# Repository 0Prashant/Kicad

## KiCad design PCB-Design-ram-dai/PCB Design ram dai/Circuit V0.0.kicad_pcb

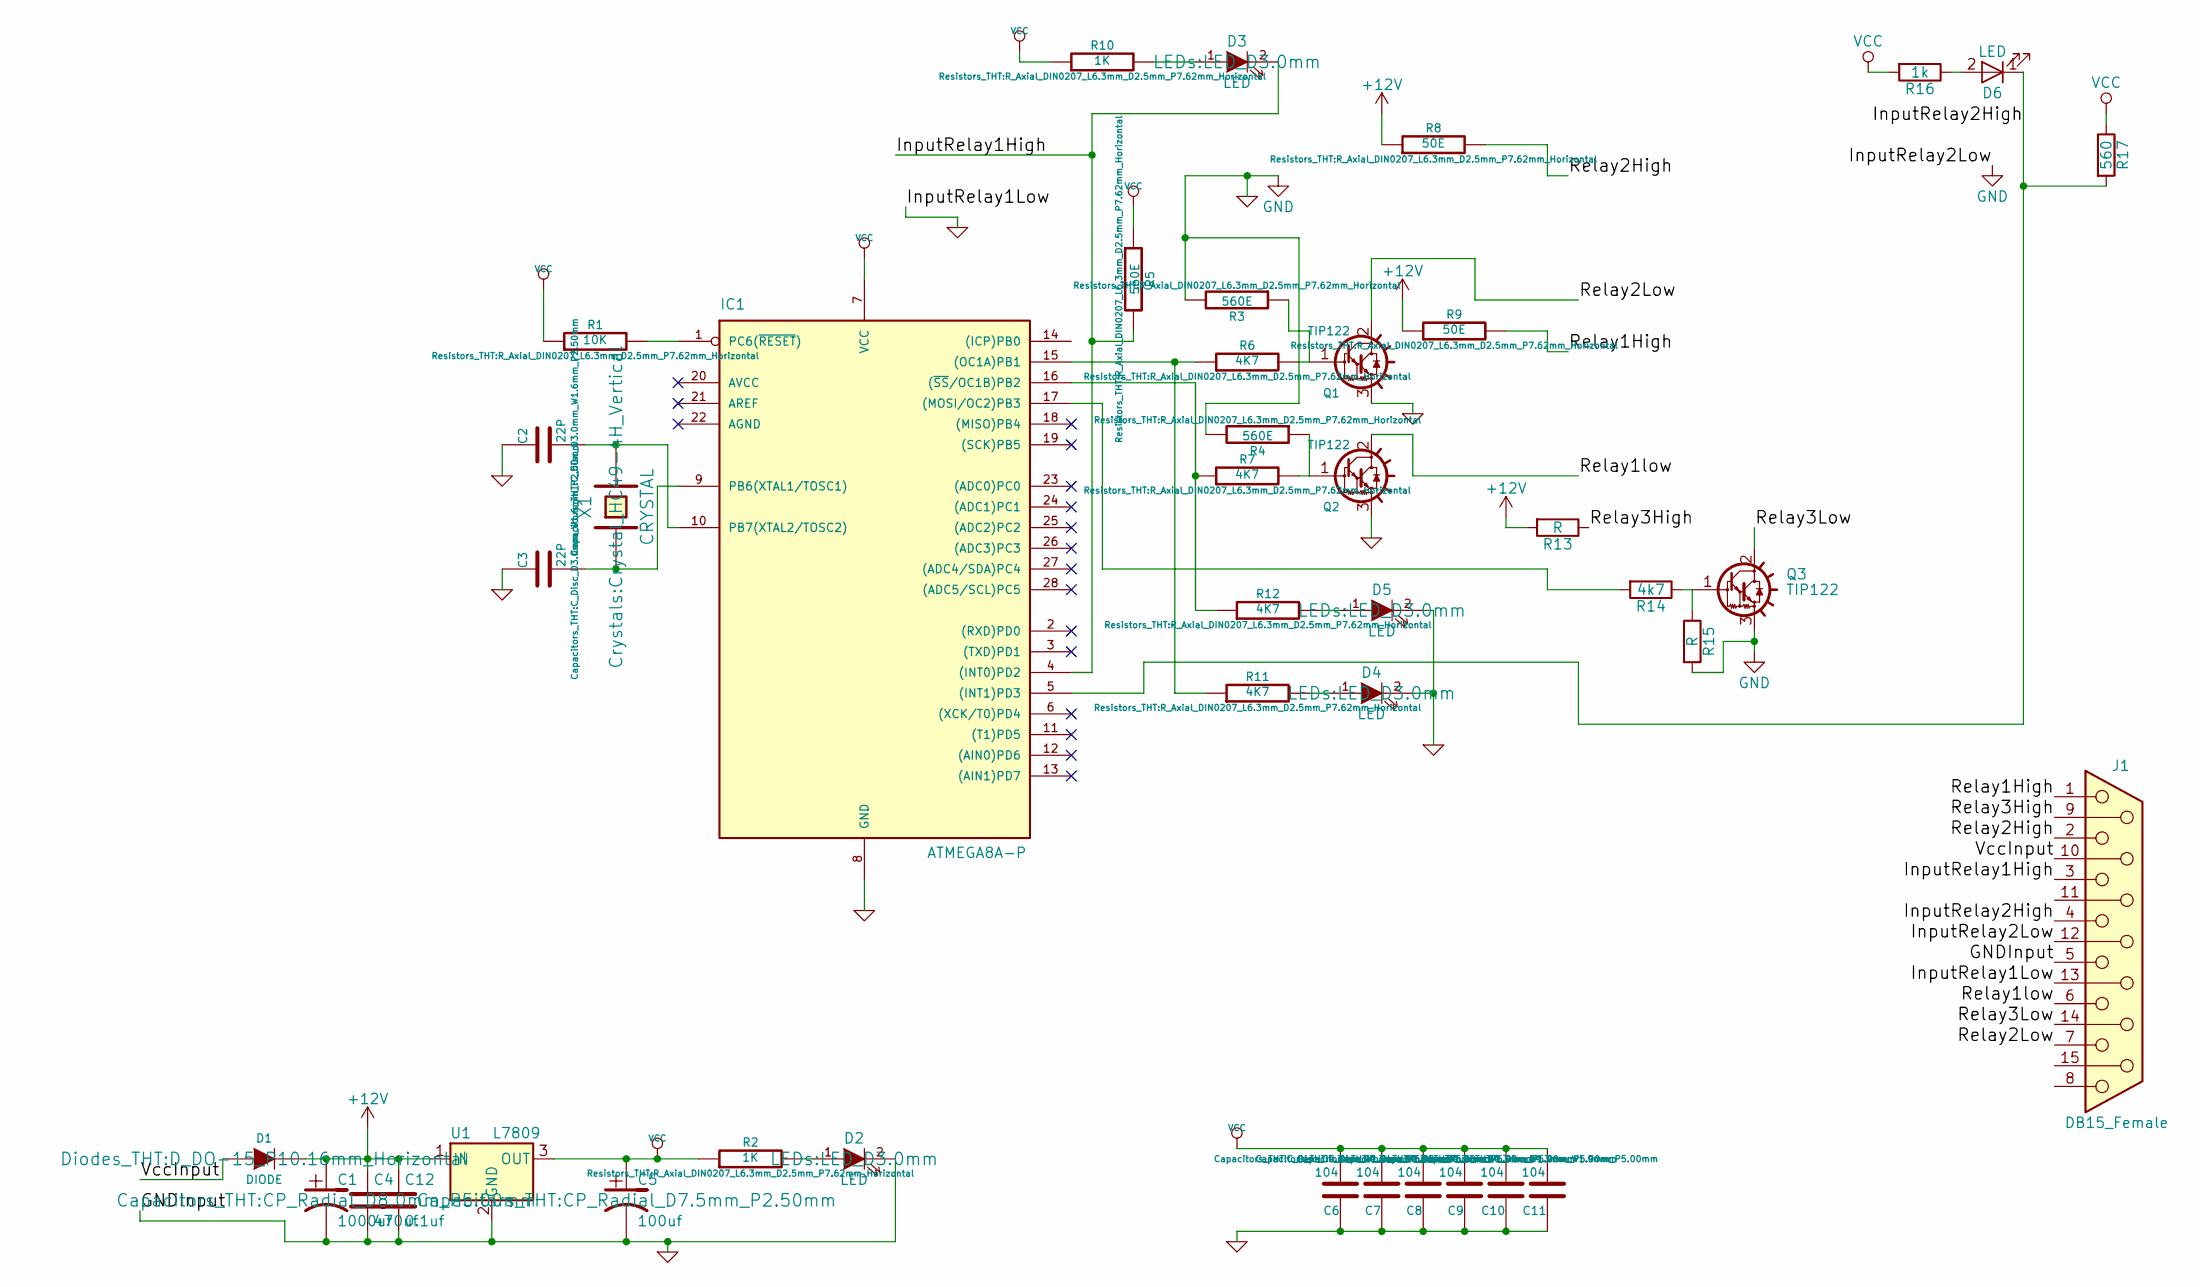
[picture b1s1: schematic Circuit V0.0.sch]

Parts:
C1: 1000uf; CP_Radial_D8.0mm_P5.00mm
C2, C3: 22P; C_Disc_D3.0mm_W1.6mm_P2.50mm
C4: 470uf; CP_Radial_D8.0mm_P3.80mm
C5: 100uf; CP_Radial_D7.5mm_P2.50mm
C6, C7, C8, C9, C10, C11: 104; C_Disc_D4.3mm_W1.9mm_P5.00mm
C12: 0.1uf; C_Disc_D4.3mm_W1.9mm_P5.00mm
D1: DIODE; D_DO-15_P10.16mm_Horizontal
D2, D3, D4, D5, D6: LED; LED_D3.0mm
IC1: ATMEGA8A-P; DIL28
J1: DB15_Female; DB15FC
Q1, Q2: TIP122; TO220
Q3: TIP122; TO-220_Vertical
R1: 10K; R_Axial_DIN0207_L6.3mm_D2.5mm_P7.62mm_Horizontal
R2, R10: 1K; R_Axial_DIN0207_L6.3mm_D2.5mm_P7.62mm_Horizontal
R3, R4, R5: 560E; R_Axial_DIN0207_L6.3mm_D2.5mm_P7.62mm_Horizontal
R6, R7, R11, R12: 4K7; R_Axial_DIN0207_L6.3mm_D2.5mm_P7.62mm_Horizontal
R8, R9: 50E; R_Axial_DIN0207_L6.3mm_D2.5mm_P7.62mm_Horizontal
R13, R15: R; R_Axial_DIN0207_L6.3mm_D2.5mm_P7.62mm_Horizontal
R14: 4k7; R_Axial_DIN0207_L6.3mm_D2.5mm_P7.62mm_Horizontal
R16: 1k; R_Axial_DIN0207_L6.3mm_D2.5mm_P7.62mm_Horizontal
R17: 560; R_Axial_DIN0207_L6.3mm_D2.5mm_P7.62mm_Horizontal
U1: L7809; TO-220
X1: CRYSTAL; Crystal_HC49-4H_Vertical

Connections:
+12V: C1.1, C4.1, C12.1, D1.2 (K), R8.1, R9.1, R13.2, U1.1 (IN)
/InputRelay1High: D3.2 (K), IC1.4 ((INT0)PD2), J1.3, R5.2
/InputRelay2High: D6.1 (K), IC1.5 ((INT1)PD3), J1.4, R17.2
/Relay1High: J1.1, R9.2
/Relay1low: J1.6, Q2.2 (C)
/Relay2High: J1.2, R8.2
/Relay2Low: J1.7, Q1.2 (C)
/Relay3High: J1.9, R13.1
/Relay3Low: J1.14, Q3.2 (C)
/VccInput: D1.1 (A), J1.10
GND: C1.2, C2.1, C3.1, C4.2, C5.2, C6.1, C7.1, C8.1, C9.1, C10.1, C11.1, C12.2, D2.2 (K), D4.2 (K), D5.2 (K), IC1.8 (GND), J1.5, J1.12, J1.13, Q1.3 (E), Q2.3 (E), Q3.3 (E), R3.2, R4.2, R15.2, U1.2 (GND)
unnamed: C2.2, IC1.10 (PB7(XTAL2/TOSC2)), X1.2
unnamed: C3.2, IC1.9 (PB6(XTAL1/TOSC1)), X1.1
unnamed: D2.1 (A), R2.2
unnamed: D3.1 (A), R10.2
unnamed: D4.1 (A), R11.2
unnamed: D5.1 (A), R12.2
unnamed: D6.2 (A), R16.1
unnamed: IC1.1 (PC6(~RESET~)), R1.2
unnamed: IC1.15 ((OC1A)PB1), R6.1, R11.1
unnamed: IC1.16 ((~SS~/OC1B)PB2), R7.1, R12.1
unnamed: IC1.17 ((MOSI/OC2)PB3), R14.2
unnamed: Q1.1 (B), R3.1, R6.2
unnamed: Q2.1 (B), R4.1, R7.2
unnamed: Q3.1 (B), R14.1, R15.1
VCC: C5.1, C6.2, C7.2, C8.2, C9.2, C10.2, C11.2, IC1.7 (VCC), R1.1, R2.1, R5.1, R10.1, R16.2, R17.1, U1.3 (OUT)

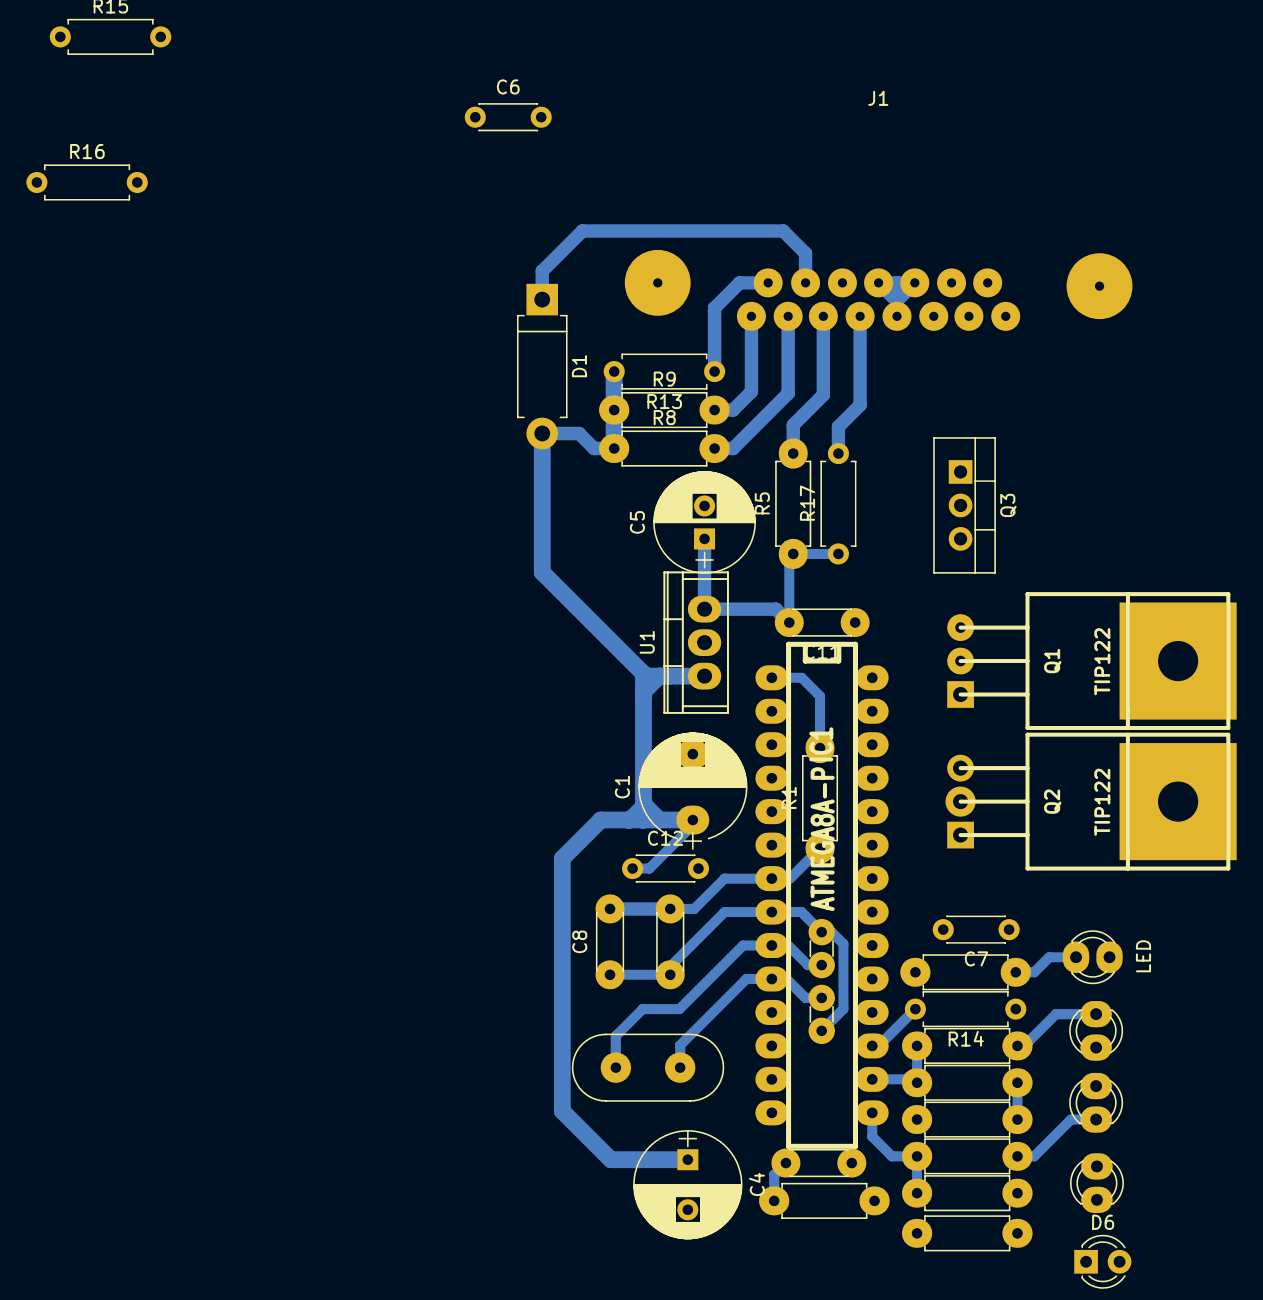
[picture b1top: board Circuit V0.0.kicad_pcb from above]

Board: 2 copper layers, 42 parts (0 on the bottom side), 26 nets.

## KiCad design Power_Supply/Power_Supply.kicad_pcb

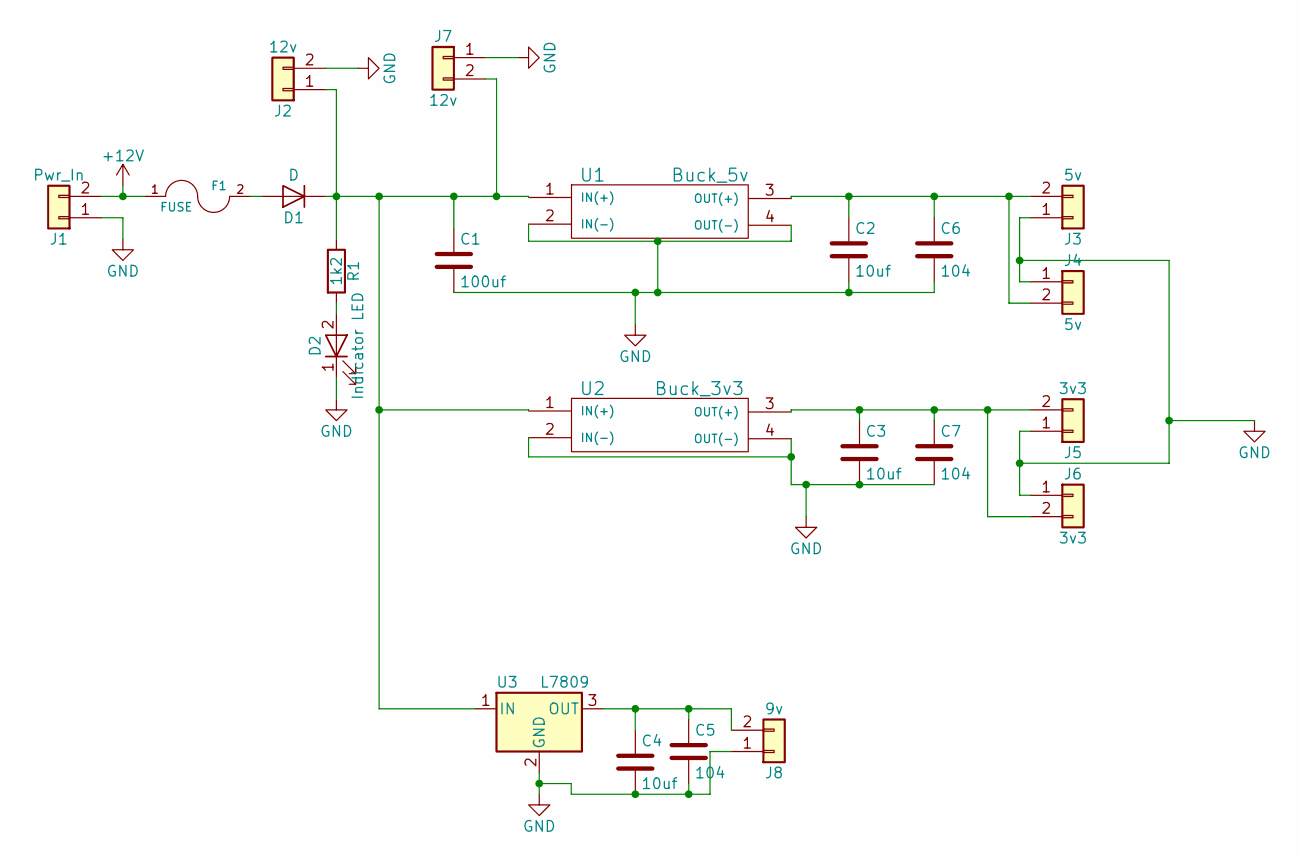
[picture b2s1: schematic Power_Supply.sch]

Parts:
C1: 100uf; Capacitor_100uF
C2, C3, C4: 10uf; Capacitor_10uF
C5, C6, C7: 104; Capacitor_Disc_Small
D1: D; Diode_Medium
D2: Indicator LED; LED_D3.0mm
F1: FUSE; Fuse_Holder
J1: Pwr_In; Solar_Connector
J2: 12v; Solar_Connector
J3, J4: 5v; Connector_Bornier_2
J5, J6: 3v3; Connector_Bornier_2
J7: 12v; Connector_Bornier_2
J8: 9v; Connector_Bornier_2
R1: 1k2; Resistor_small
U1: Buck_5v; Buck_Regulator
U2: Buck_3v3; Buck_Regulator
U3: L7809; Voltage_Regulators

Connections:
+12V: F1.1, J1.2
GND: C1.2, C2.2, C3.2, C4.2, C5.2, C6.2, C7.2, D2.1 (K), J1.1, J2.2, J3.1, J4.1, J5.1, J6.1, J7.1, J8.1, U1.2 (IN(-)), U1.4 (OUT(-)), U2.2 (IN(-)), U2.4 (OUT(-)), U3.2 (GND)
unnamed: C1.1, D1.1 (K), J2.1, J7.2, R1.1, U1.1 (IN(+)), U2.1 (IN(+)), U3.1 (IN)
unnamed: C2.1, C6.1, J3.2, J4.2, U1.3 (OUT(+))
unnamed: C3.1, C7.1, J5.2, J6.2, U2.3 (OUT(+))
unnamed: C4.1, C5.1, J8.2, U3.3 (OUT)
unnamed: D1.2 (A), F1.2
unnamed: D2.2 (A), R1.2

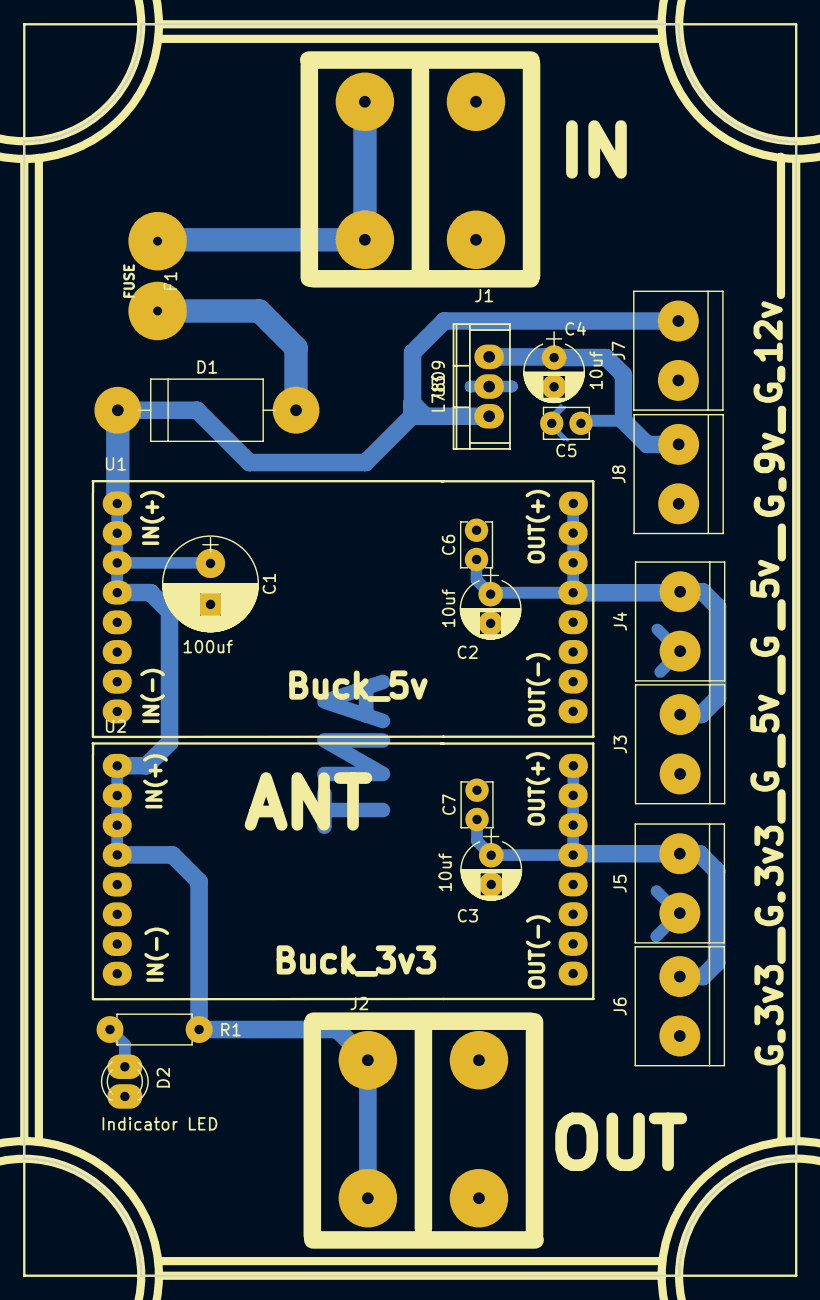
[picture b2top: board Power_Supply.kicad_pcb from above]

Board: 2 copper layers, 66.0 x 107.0 mm, 22 parts (0 on the bottom side), 8 nets.

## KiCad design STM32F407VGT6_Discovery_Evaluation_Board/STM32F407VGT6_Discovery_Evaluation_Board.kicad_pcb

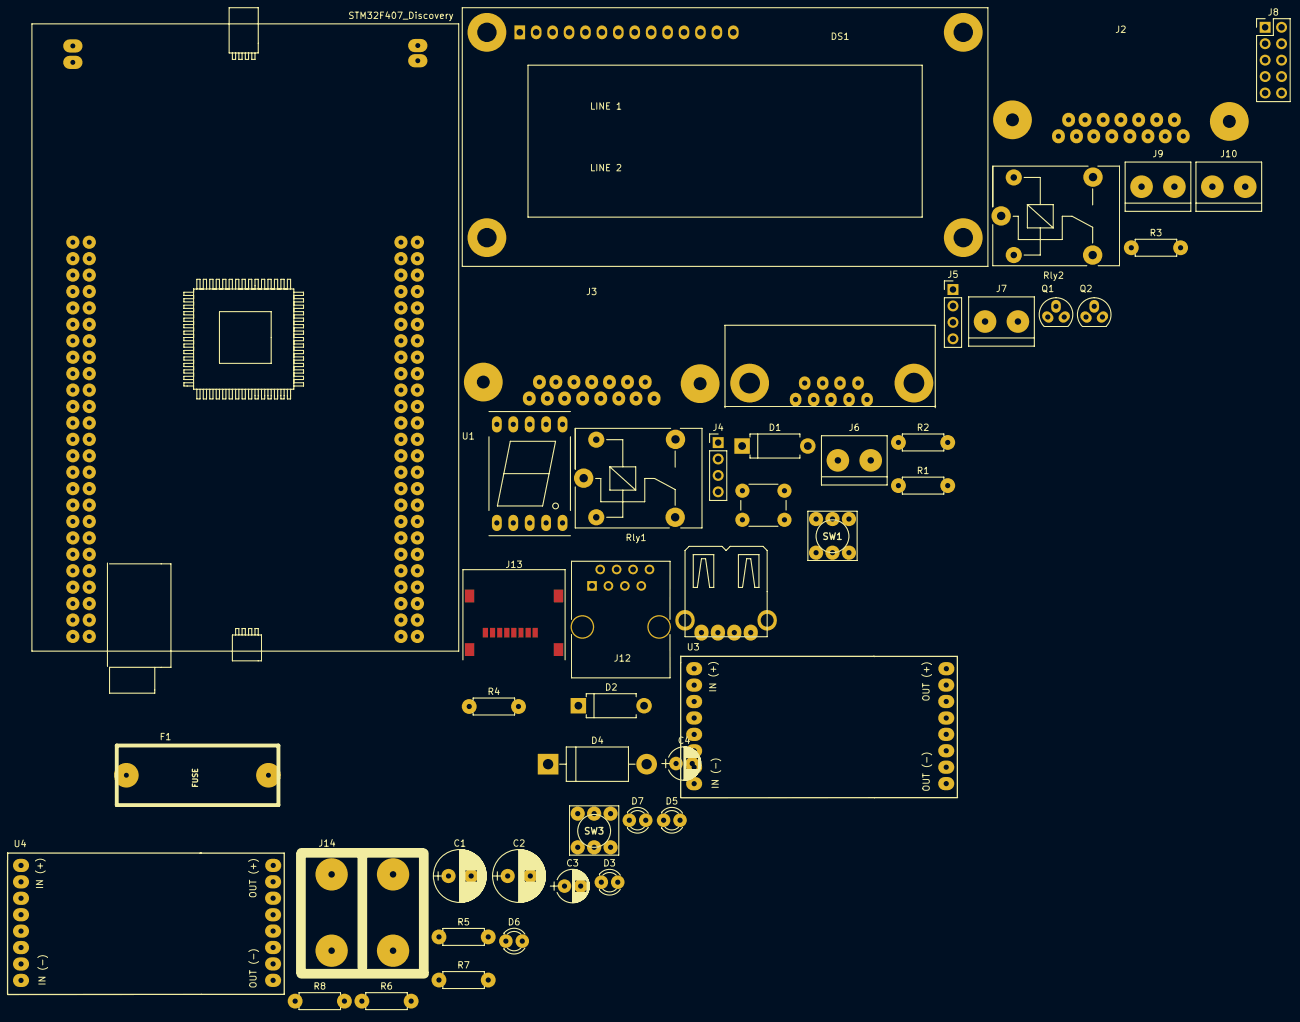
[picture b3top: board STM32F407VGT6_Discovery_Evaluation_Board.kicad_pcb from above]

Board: 2 copper layers, 46 parts (0 on the bottom side), 23 nets, no tracks yet.

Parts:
C1, C2: C; Capacitor_100uF
C3, C4: C; Capacitor_10uF
D1, D2: D; Diode_Small
D3, D5, D6, D7: LED; LED_D3.0mm
D4: D; Diode_Medium
DS1: LCD16X2; LCD_ALPHA
F1: FUSE; Fuse_Holder
J1: encode; Connector_DB_9
J2: motor; Connector_DB15
J3: other; Connector_DB15
J4: uart; Pin_Header_Straight_1x04_Pitch2.54mm
J5: i2c; Pin_Header_Straight_1x04_Pitch2.54mm
J6, J7: relay; Connector_Bornier_2
J8: vcc gnd; Pin_Header_Straight_2x05_Pitch2.54mm
J9: 3v3; Connector_Bornier_2
J10: 5v; Connector_Bornier_2
J11: USB_A; Connector_USB
J12: RJ45; RJ45_8
J13: Micro_SD_Card; MicroSd_Wurth_693072010801
J14: Power_In; Solar_Connector
Q1, Q2: BC547
R1, R2, R3, R4, R5, R6, R7, R8: R; Resistor_small
Rly1, Rly2: 6V_Relay; Relay_6V
SW1: dip; DIP_Switch
SW2: Push; Push_Button
SW3: SW_DIP_x01; DIP_Switch
U1: 7SEGMENT_CC; 7SegmentLED_LTS6760_LTS6780
U2: STM32F407_Discovery
U3, U4: Buck; Buck_Regulator

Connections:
+3V3: C3.1, R8.1, U4.3
+5V: C4.1, R7.1, U3.3
+12V: C1.1, C2.1, D4.1, R6.1, U3.1, U4.1
GND: C1.2, C2.2, C3.2, C4.2, D3.1, D5.1, D6.1, D7.1, J14.1, Q1.3, Q2.3, R1.2, R2.2, U3.2, U3.4, U4.2, U4.4
unnamed: D1.1, Rly1.5
unnamed: D1.2, Q1.1, Rly1.1
unnamed: D2.1, Rly2.5
unnamed: D2.2, Q2.1, Rly2.1
unnamed: D3.2, R5.2
unnamed: D4.2, F1.2
unnamed: D5.2, R6.2
unnamed: D6.2, R7.2
unnamed: D7.2, R8.2
unnamed: F1.1, SW3.2
unnamed: J6.1, Rly1.3
unnamed: J6.2, Rly1.2
unnamed: J7.1, Rly2.3
unnamed: J7.2, Rly2.2
unnamed: J14.2, R5.1, SW3.1
unnamed: Q1.2, R3.1
unnamed: Q2.2, R4.1
unnamed: R1.1, R3.2
unnamed: R2.1, R4.2

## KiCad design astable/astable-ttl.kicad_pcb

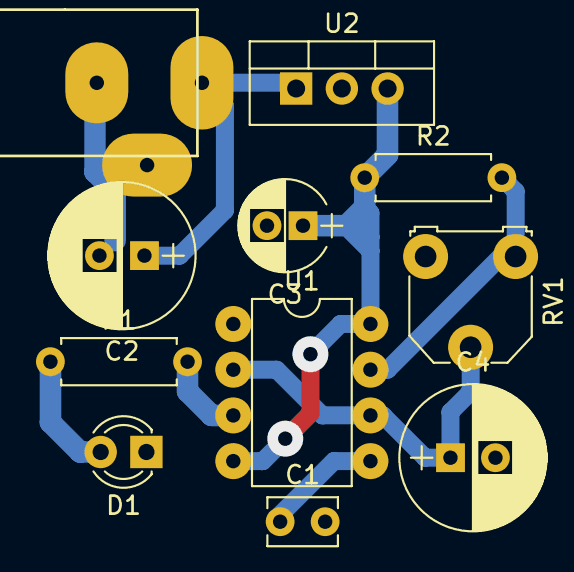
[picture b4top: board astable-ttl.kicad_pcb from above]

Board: 2 copper layers, 11 parts (0 on the bottom side), 8 nets.

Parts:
C1: 0.1UF; C_Disc_D3.8mm_W2.6mm_P2.50mm
C2, C4: 100UF; CP_Radial_D8.0mm_P2.50mm
C3: 10UF; CP_Radial_D5.0mm_P2.00mm
D1: LED; LED_D3.0mm
R1: 330; R_Axial_DIN0207_L6.3mm_D2.5mm_P7.62mm_Horizontal
R2: 5K; R_Axial_DIN0207_L6.3mm_D2.5mm_P7.62mm_Horizontal
RV1: POT; Potentiometer_Triwood_RM-065
U1: NE555; DIP-8_W7.62mm
U2: L7805; TO-220_Vertical
U3: Barrel_jack

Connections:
/VCC: C3.1, R2.1, U1.4, U1.8, U2.3
GND: C1.2, C2.2, C3.2, C4.2, D1.1, U1.1, U2.2, U3.2
unnamed: C1.1, U1.5
unnamed: C2.1, U2.1, U3.1
unnamed: C4.1, RV1.2, U1.2, U1.6
unnamed: D1.2, R1.1
unnamed: R1.2, U1.3
unnamed: R2.2, RV1.1, U1.7

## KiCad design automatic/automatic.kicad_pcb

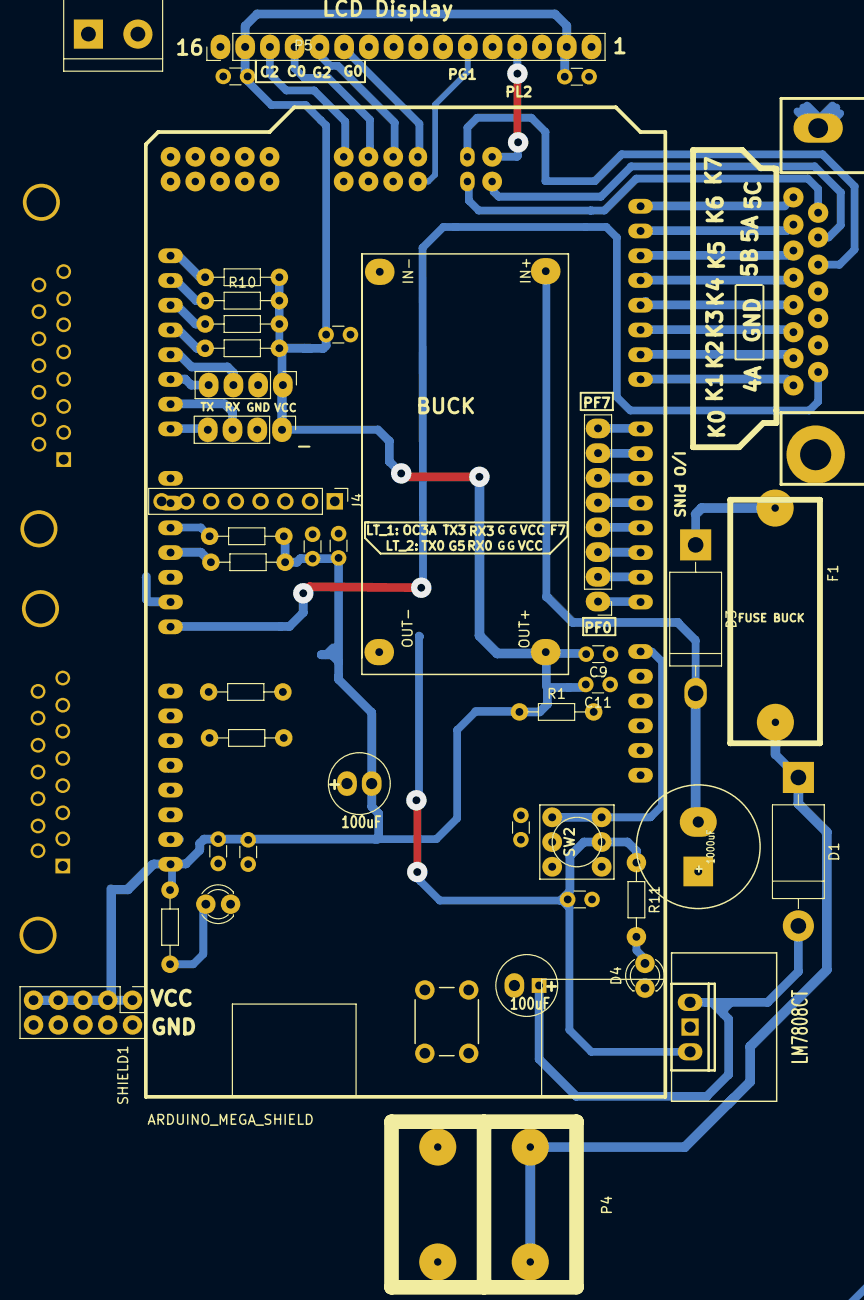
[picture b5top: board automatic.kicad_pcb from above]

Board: 2 copper layers, 46 parts (0 on the bottom side), 64 nets.

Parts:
C1, C14: 100uF; c_100
C2: 104Pf; C_Disc_D3.0mm_W1.6mm_P2.50mm
C3: 10uF; C_Disc_D3.0mm_W1.6mm_P2.50mm
C4, C5, C6, C7, C8, C9, C10, C11, C12: 104; C_Disc_D3.0mm_W1.6mm_P2.50mm
C13: 1000uF; c_1000
D1, D3: DIODE; D_DO-201AD_P15.24mm_Horizontal
D2, D4: LED; LED_D3.0mm
F1: FUSE BUCK; FUSE
J1: DB15; DB15MC
J2: LINE TRACKER; DB15FC
J3: LCD Display; Pin_Header_Straight_1x16_Pitch2.54mm
J4: CONN_01X08; Pin_Header_Straight_1x08_Pitch2.54mm
J5: DB15; DB15FC
J7: I/O_2; Pin_Header_Straight_1x08_Pitch2.54mm
P1: BlueTh2; Pin_Header_Straight_1x04_Pitch2.54mm
P2: BlueTh3; Pin_Header_Straight_1x04_Pitch2.54mm
P3: CONN_5X2; Pin_Header_Straight_2x05_Pitch2.54mm
P4: BATTERY; SOLAR_CONNECTOR
P5: BUCK REG; Buck_reg_mod
P6: CONN_2; bornier2
R1, R3, R4, R5, R6, R8, R10: 10K; R_Axial_DIN0204_L3.6mm_D1.6mm_P7.62mm_Horizontal
R2, R11: 330; R_Axial_DIN0204_L3.6mm_D1.6mm_P7.62mm_Horizontal
R7, R9: 1K; R_Axial_DIN0204_L3.6mm_D1.6mm_P7.62mm_Horizontal
SHIELD1: ARDUINO_MEGA_SHIELD; ARUDINO_MEGA_SHIELD
SW1: SW_PUSH; SW_PUSH_6mm
SW2: SW_PUSH; SPST_SMALL
U1: LM7808CT; LM78_heatsink

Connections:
/9V: C3.1, R11.1, SW2.1, U1.3
/12V: D1.1, F1.1, P4.1
/E: J3.11, SHIELD1.40
/GND: C1.2, C2.2, C3.2, C4.2, C5.1, C6.2, C7.1, C8.2, C9.1, C10.2, C11.1, C12.2, C13.1, C14.1, D2.1, D4.1, J1.10, J1.11, J1.12, J3.1, J3.12, J3.16, J5.15, P1.2, P2.2, P3.2, P3.4, P3.6, P3.8, P3.10, P4.2, P5.1, P5.3, SHIELD1.GND1, SHIELD1.GND2, SHIELD1.GND3, SW1.2, U1.2
/INT0: R8.1, SHIELD1.21
/INT1: R10.1, SHIELD1.20
/INT2: J5.13, R3.1, SHIELD1.19
/INT3: J5.6, R4.1, SHIELD1.18
/INT4: J5.14, R5.1, SHIELD1.2
/INT5: J5.7, R6.1, SHIELD1.3
/JPULSE1: J2.12, SHIELD1.9
/JPULSE2: J2.4, SHIELD1.10
/OC4A: J1.9, SHIELD1.6
/OC4C: R9.1, SHIELD1.8
/OC5A: J1.14, SHIELD1.46
/OC5B: J1.13, SHIELD1.45
/OC5C: J1.15, SHIELD1.44
/PA0: J5.2, SHIELD1.22
/PA1: J5.1, SHIELD1.23
/PA2: J5.10, SHIELD1.24
/PA3: J5.9, SHIELD1.25
/PA4: J5.3, SHIELD1.26
/PA5: J5.11, SHIELD1.27
/PA6: J2.14, P6.1, SHIELD1.28
/PA7: J2.6, P6.2, SHIELD1.29
/PC0: J3.4, J4.8, SHIELD1.37
/PC1: J4.7, SHIELD1.36
/PC2: J3.3, J4.6, SHIELD1.35
/PC3: J4.5, SHIELD1.34
/PF0: J7.1, SHIELD1.AD0
/PF1: J7.2, SHIELD1.AD1
/PF2: J7.3, SHIELD1.AD2
/PF3: J7.4, SHIELD1.AD3
/PF4: J7.5, SHIELD1.AD4
/PF5: J7.6, SHIELD1.AD5
/PF6: J7.7, SHIELD1.AD6
/PF7: J7.8, SHIELD1.AD7
/PG0: J3.6, SHIELD1.41
/PG2: J3.5, SHIELD1.39
/PK0: J1.1, SHIELD1.AD8
/PK1: J1.2, SHIELD1.AD9
/PK2: J1.3, SHIELD1.AD10
/PK3: J1.4, SHIELD1.AD11
/PK4: J1.5, SHIELD1.AD12
/PK5: J1.6, SHIELD1.AD13
/PK6: J1.7, SHIELD1.AD14
/PK7: J1.8, SHIELD1.AD15
/PL2: J3.13, SHIELD1.47
/RESET: C2.1, R1.2, SHIELD1.RST, SW1.1
/RX0: J2.3, SHIELD1.0
/RX2: J2.2, P1.3, SHIELD1.17
/RX3: P2.3, SHIELD1.15
/TX0: J2.11, SHIELD1.1
/TX2: J2.10, P1.4, SHIELD1.16
/TX3: P2.4, SHIELD1.14
/UEN1: J2.13, SHIELD1.11
/UEN2: J2.5, SHIELD1.12
/VCC: C4.1, C5.2, C6.1, C7.2, C8.1, C9.2, C10.1, C11.2, C12.1, C14.2, J3.2, J3.15, J5.8, P1.1, P2.1, P3.1, P3.3, P3.5, P3.7, P3.9, P5.4, R1.1, R2.1, R3.2, R4.2, R5.2, R6.2, R8.2, R10.2, SHIELD1.AREF
/VIN: SHIELD1.V_IN, SW2.2
unnamed: C1.1, D1.2, U1.1
unnamed: C13.2, D3.2, P5.2
unnamed: D2.2, R2.2
unnamed: D3.1, F1.2
unnamed: D4.2, R11.2

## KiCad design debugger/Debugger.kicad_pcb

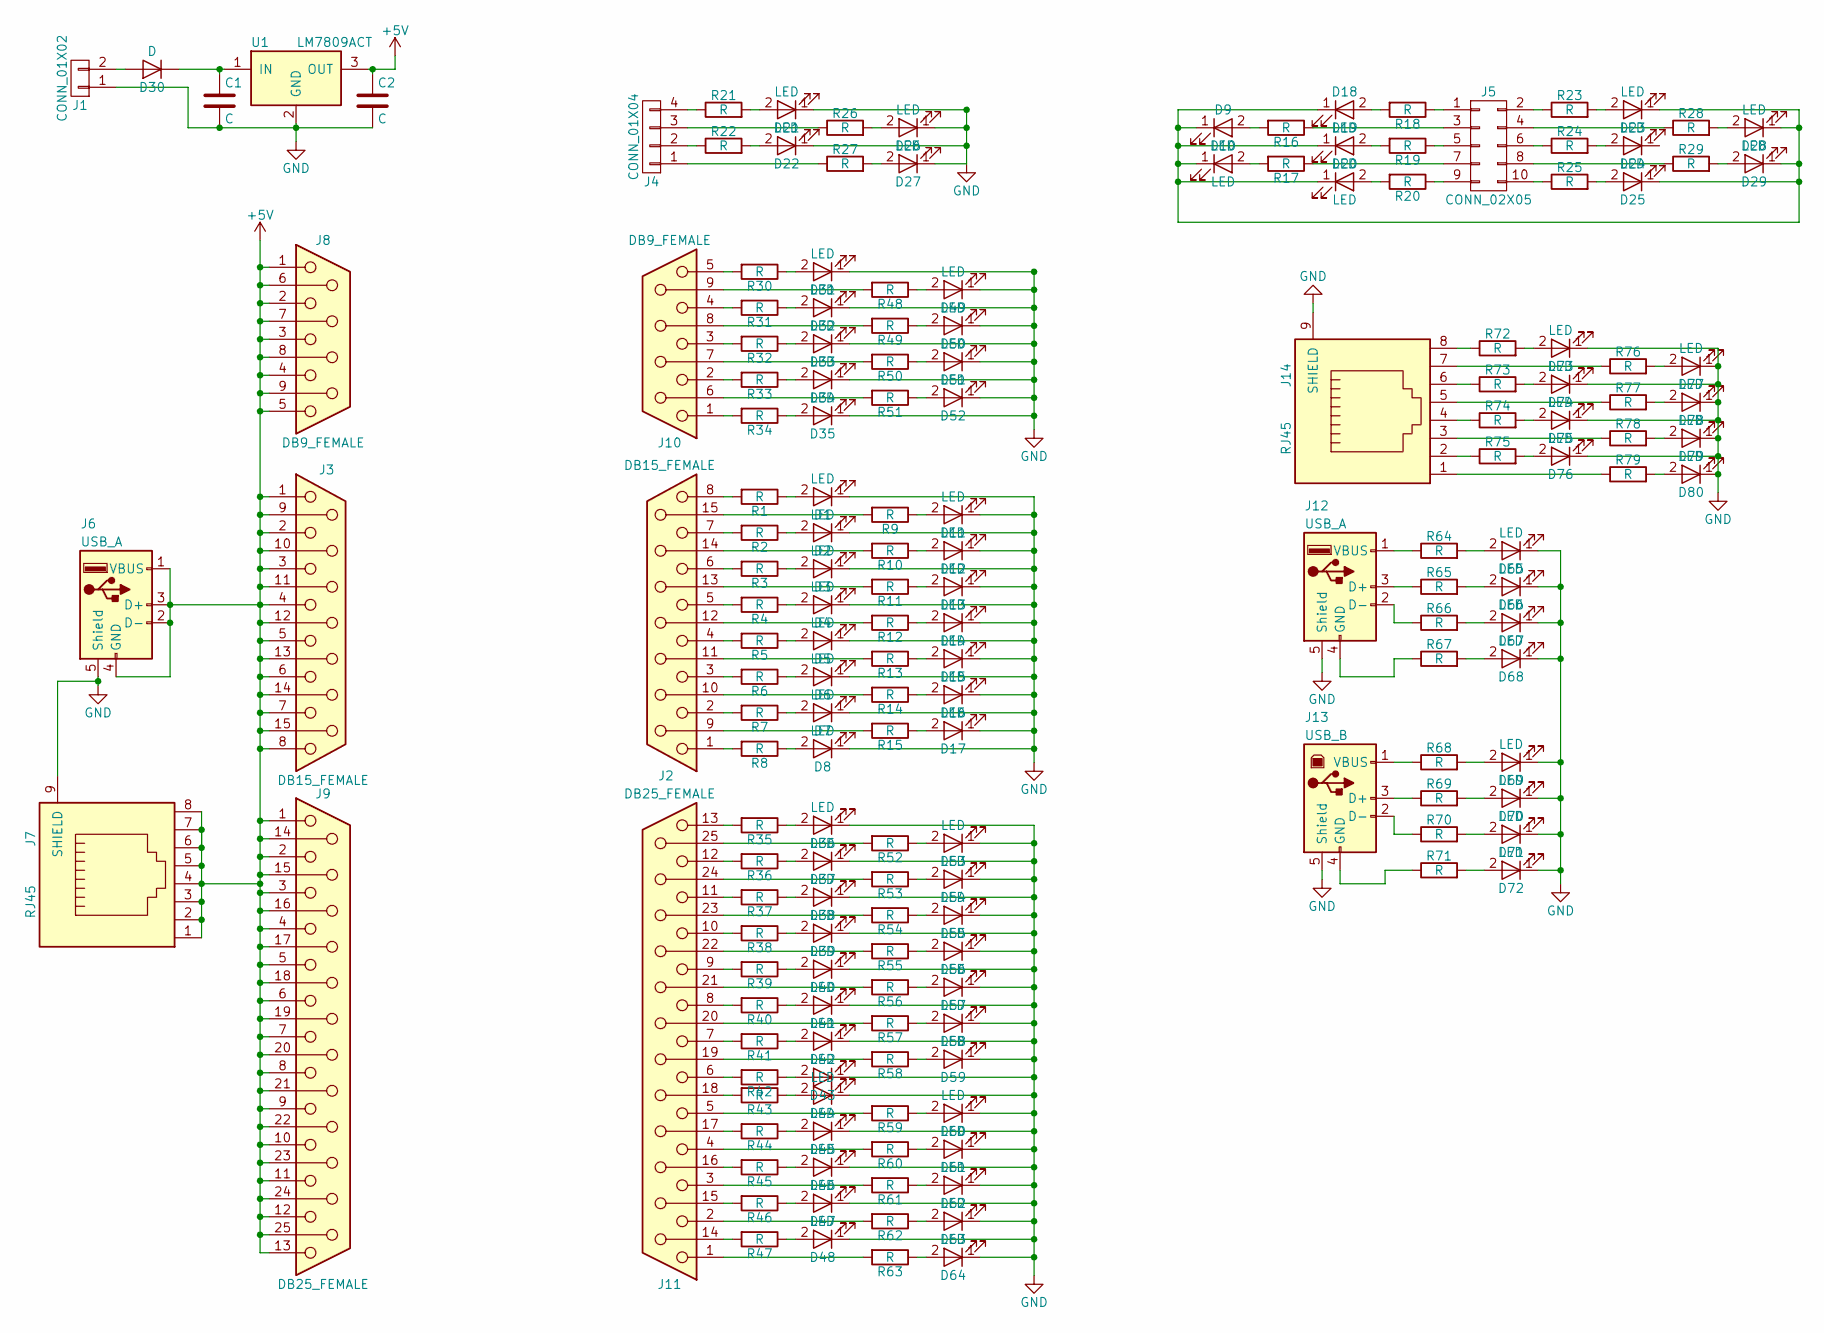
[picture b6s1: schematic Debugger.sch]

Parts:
C1: C; Capacitor_100uF
C2: C; Capacitor_10uF
D1, D2, D3, D4, D5, D6, D7, D8, D9, D10, D11, D12, D13, D14, D15, D16, D17, D18, D19, D20, D21, D22, D23, D24, D25, D26, D27, D28, D29, D31, D32, D33, D34, D35, D36, D37, D38, D39, D40, D41, D42, D43, D44, D45, D46, D47, D48, D49, D50, D51, D52, D53, D54, D55, D56, D57, D58, D59, D60, D61, D62, D63, D64, D65, D66, D67, D68, D69, D70, D71, D72, D73, D74, D75, D76, D77, D78, D79, D80: LED; LED_D3.0mm
D30: D; Diode_Small
J1: CONN_01X02; Connector_Bornier_2
J2, J3: DB15_FEMALE; Connector_DB15
J4: CONN_01X04; Pin_Header_Straight_1x04_Pitch2.54mm
J5: CONN_02X05; Pin_Header_Straight_2x05_Pitch2.54mm
J6, J12: USB_A; Connector_USB
J7, J14: RJ45; RJ45_TRANSFO_ver2
J8, J10: DB9_FEMALE; Connector_DB_9
J9, J11: DB25_FEMALE; Connector_DB25
J13: USB_B
R1, R2, R3, R4, R5, R6, R7, R8, R9, R10, R11, R12, R13, R14, R15, R16, R17, R18, R19, R20, R21, R22, R23, R24, R25, R26, R27, R28, R29, R30, R31, R32, R33, R34, R35, R36, R37, R38, R39, R40, R41, R42, R43, R44, R45, R46, R47, R48, R49, R50, R51, R52, R53, R54, R55, R56, R57, R58, R59, R60, R61, R62, R63, R64, R65, R66, R67, R68, R69, R70, R71, R72, R73, R74, R75, R76, R77, R78, R79: R; Resistor_small
U1: LM7809ACT; Voltage_Regulators

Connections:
+5V: C2.1, J3.1, J3.2, J3.3, J3.4, J3.5, J3.6, J3.7, J3.8, J3.9, J3.10, J3.11 (P111), J3.12, J3.13, J3.14, J3.15, J6.1 (VBUS), J6.2 (D-), J6.3 (D+), J6.4 (GND), J7.1, J7.2, J7.3, J7.4, J7.5, J7.6, J7.7, J7.8, J8.1, J8.2, J8.3, J8.4, J8.5, J8.6, J8.7, J8.8, J8.9, J9.1, J9.2, J9.3, J9.4, J9.5, J9.6, J9.7, J9.8, J9.9, J9.10, J9.11, J9.12, J9.13, J9.14, J9.15, J9.16, J9.17, J9.18, J9.19, J9.20, J9.21, J9.22, J9.23, J9.24, J9.25, U1.3 (OUT)
GND: C1.2, C2.2, D1.1 (K), D2.1 (K), D3.1 (K), D4.1 (K), D5.1 (K), D6.1 (K), D7.1 (K), D8.1 (K), D11.1 (K), D12.1 (K), D13.1 (K), D14.1 (K), D15.1 (K), D16.1 (K), D17.1 (K), D21.1 (K), D22.1 (K), D26.1 (K), D27.1 (K), D31.1 (K), D32.1 (K), D33.1 (K), D34.1 (K), D35.1 (K), D36.1 (K), D37.1 (K), D38.1 (K), D39.1 (K), D40.1 (K), D41.1 (K), D42.1 (K), D43.1 (K), D44.1 (K), D45.1 (K), D46.1 (K), D47.1 (K), D48.1 (K), D49.1 (K), D50.1 (K), D51.1 (K), D52.1 (K), D53.1 (K), D54.1 (K), D55.1 (K), D56.1 (K), D57.1 (K), D58.1 (K), D59.1 (K), D60.1 (K), D61.1 (K), D62.1 (K), D63.1 (K), D64.1 (K), D65.1 (K), D66.1 (K), D67.1 (K), D68.1 (K), D69.1 (K), D70.1 (K), D71.1 (K), D72.1 (K), D73.1 (K), D74.1 (K), D75.1 (K), D76.1 (K), D77.1 (K), D78.1 (K), D79.1 (K), D80.1 (K), J1.1, J6.5 (Shield), J7.9 (SHIELD), J12.5 (Shield), J13.5 (Shield), J14.9 (SHIELD), U1.2 (GND)
unnamed: C1.1, D30.1 (K), U1.1 (IN)
unnamed: D1.2 (A), R1.1
unnamed: D2.2 (A), R2.1
unnamed: D3.2 (A), R3.1
unnamed: D4.2 (A), R4.1
unnamed: D5.2 (A), R5.1
unnamed: D6.2 (A), R6.1
unnamed: D7.2 (A), R7.1
unnamed: D8.2 (A), R8.1
unnamed: D9.2 (A), R16.2
unnamed: D9.1 (K), D10.1 (K), D18.1 (K), D19.1 (K), D20.1 (K), D23.1 (K), D25.1 (K), D28.1 (K), D29.1 (K)
unnamed: D10.2 (A), R17.2
unnamed: D11.2 (A), R9.1
unnamed: D12.2 (A), R10.1
unnamed: D13.2 (A), R11.1
unnamed: D14.2 (A), R12.1
unnamed: D15.2 (A), R13.1
unnamed: D16.2 (A), R14.1
unnamed: D17.2 (A), R15.1
unnamed: D18.2 (A), R18.2
unnamed: D19.2 (A), R19.2
unnamed: D20.2 (A), R20.2
unnamed: D21.2 (A), R21.2
unnamed: D22.2 (A), R22.2
unnamed: D23.2 (A), R23.2
unnamed: D24.2 (A), R24.2
unnamed: D25.2 (A), R25.2
unnamed: D26.2 (A), R26.2
unnamed: D27.2 (A), R27.2
unnamed: D28.2 (A), R28.2
unnamed: D29.2 (A), R29.2
unnamed: D30.2 (A), J1.2
unnamed: D31.2 (A), R30.1
unnamed: D32.2 (A), R31.1
unnamed: D33.2 (A), R32.1
unnamed: D34.2 (A), R33.1
unnamed: D35.2 (A), R34.1
unnamed: D36.2 (A), R35.1
unnamed: D37.2 (A), R36.1
unnamed: D38.2 (A), R37.1
unnamed: D39.2 (A), R38.1
unnamed: D40.2 (A), R39.1
unnamed: D41.2 (A), R40.1
unnamed: D42.2 (A), R41.1
unnamed: D43.2 (A), R42.1
unnamed: D44.2 (A), R43.1
unnamed: D45.2 (A), R44.1
unnamed: D46.2 (A), R45.1
unnamed: D47.2 (A), R46.1
unnamed: D48.2 (A), R47.1
unnamed: D49.2 (A), R48.1
unnamed: D50.2 (A), R49.1
unnamed: D51.2 (A), R50.1
unnamed: D52.2 (A), R51.1
unnamed: D53.2 (A), R52.1
unnamed: D54.2 (A), R53.1
unnamed: D55.2 (A), R54.1
unnamed: D56.2 (A), R55.1
unnamed: D57.2 (A), R56.1
unnamed: D58.2 (A), R57.1
unnamed: D59.2 (A), R58.1
unnamed: D60.2 (A), R59.1
unnamed: D61.2 (A), R60.1
unnamed: D62.2 (A), R61.1
unnamed: D63.2 (A), R62.1
unnamed: D64.2 (A), R63.1
unnamed: D65.2 (A), R64.2
unnamed: D66.2 (A), R65.2
unnamed: D67.2 (A), R66.2
unnamed: D68.2 (A), R67.2
unnamed: D69.2 (A), R68.2
unnamed: D70.2 (A), R69.2
unnamed: D71.2 (A), R70.2
unnamed: D72.2 (A), R71.2
unnamed: D73.2 (A), R72.2
unnamed: D74.2 (A), R73.2
unnamed: D75.2 (A), R74.2
unnamed: D76.2 (A), R75.2
unnamed: D77.2 (A), R76.2
unnamed: D78.2 (A), R77.2
unnamed: D79.2 (A), R78.2
unnamed: D80.2 (A), R79.2
unnamed: J2.1, R8.2
unnamed: J2.2, R7.2
unnamed: J2.3, R6.2
unnamed: J2.4, R5.2
unnamed: J2.5, R4.2
unnamed: J2.6, R3.2
unnamed: J2.7, R2.2
unnamed: J2.8, R1.2
unnamed: J2.9, R15.2
unnamed: J2.10, R14.2
unnamed: J2.11 (P111), R13.2
unnamed: J2.12, R12.2
unnamed: J2.13, R11.2
unnamed: J2.14, R10.2
unnamed: J2.15, R9.2
unnamed: J4.1, R27.1
unnamed: J4.2, R22.1
unnamed: J4.3, R26.1
unnamed: J4.4, R21.1
unnamed: J5.1, R18.1
unnamed: J5.2, R23.1
unnamed: J5.3, R16.1
unnamed: J5.4, R28.1
unnamed: J5.5, R19.1
unnamed: J5.6, R24.1
unnamed: J5.7, R17.1
unnamed: J5.8, R29.1
unnamed: J5.9, R20.1
unnamed: J5.10, R25.1
unnamed: J10.1, R34.2
unnamed: J10.2, R33.2
unnamed: J10.3, R32.2
unnamed: J10.4, R31.2
unnamed: J10.5, R30.2
unnamed: J10.6, R51.2
unnamed: J10.7, R50.2
unnamed: J10.8, R49.2
unnamed: J10.9, R48.2
unnamed: J11.1, R63.2
unnamed: J11.2, R62.2
unnamed: J11.3, R61.2
unnamed: J11.4, R60.2
unnamed: J11.5, R59.2
unnamed: J11.6, R42.2
unnamed: J11.7, R41.2
unnamed: J11.8, R40.2
unnamed: J11.9, R39.2
unnamed: J11.10, R38.2
unnamed: J11.11, R37.2
unnamed: J11.12, R36.2
unnamed: J11.13, R35.2
unnamed: J11.14, R47.2
unnamed: J11.15, R46.2
unnamed: J11.16, R45.2
unnamed: J11.17, R44.2
unnamed: J11.18, R43.2
unnamed: J11.19, R58.2
unnamed: J11.20, R57.2
unnamed: J11.21, R56.2
unnamed: J11.22, R55.2
unnamed: J11.23, R54.2
unnamed: J11.24, R53.2
unnamed: J11.25, R52.2
unnamed: J12.1 (VBUS), R64.1
unnamed: J12.2 (D-), R66.1
unnamed: J12.3 (D+), R65.1
unnamed: J12.4 (GND), R67.1
unnamed: J13.1 (VBUS), R68.1
unnamed: J13.2 (D-), R70.1
unnamed: J13.3 (D+), R69.1
unnamed: J13.4 (GND), R71.1
unnamed: J14.1, R79.1
unnamed: J14.2, R75.1
unnamed: J14.3, R78.1
unnamed: J14.4, R74.1
unnamed: J14.5, R77.1
unnamed: J14.6, R73.1
unnamed: J14.7, R76.1
unnamed: J14.8, R72.1

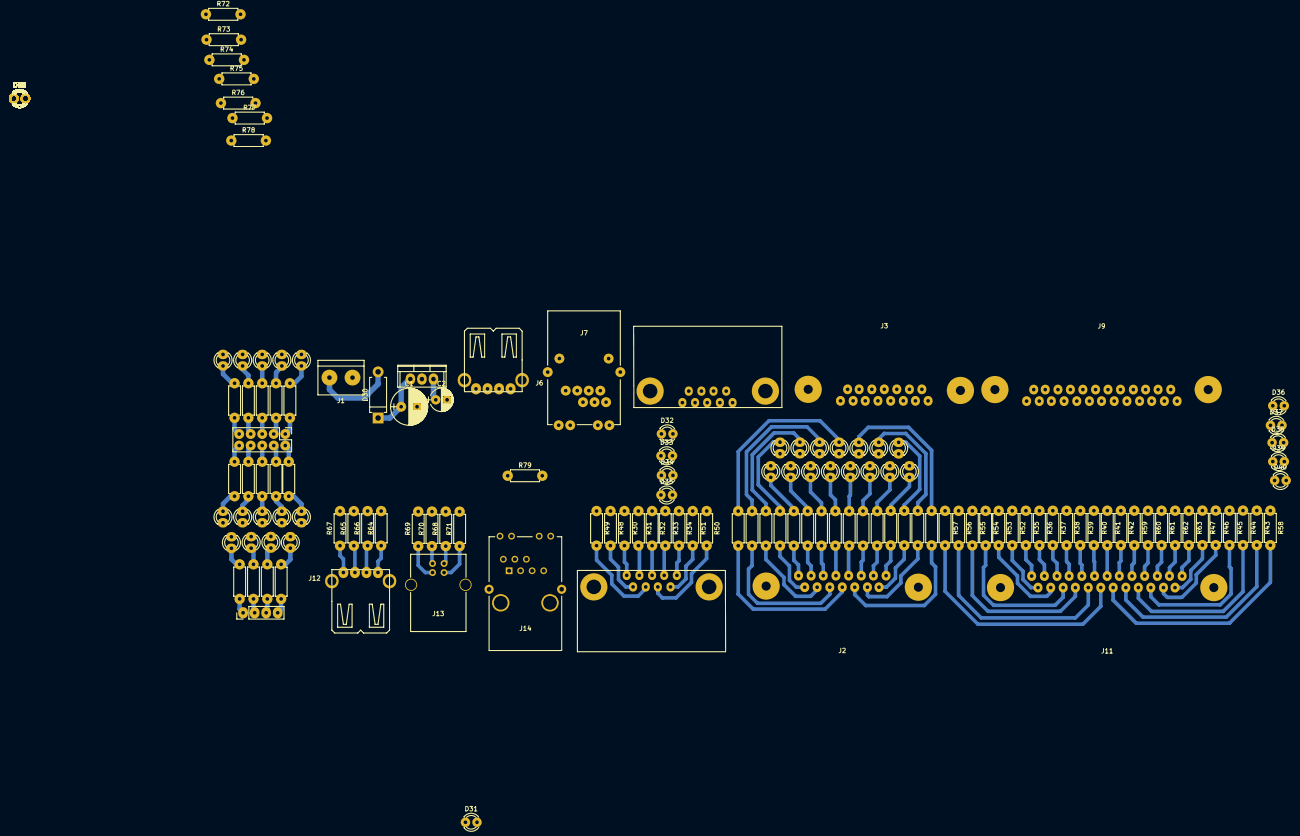
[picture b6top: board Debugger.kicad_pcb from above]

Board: 2 copper layers, 176 parts (0 on the bottom side), 162 nets.
